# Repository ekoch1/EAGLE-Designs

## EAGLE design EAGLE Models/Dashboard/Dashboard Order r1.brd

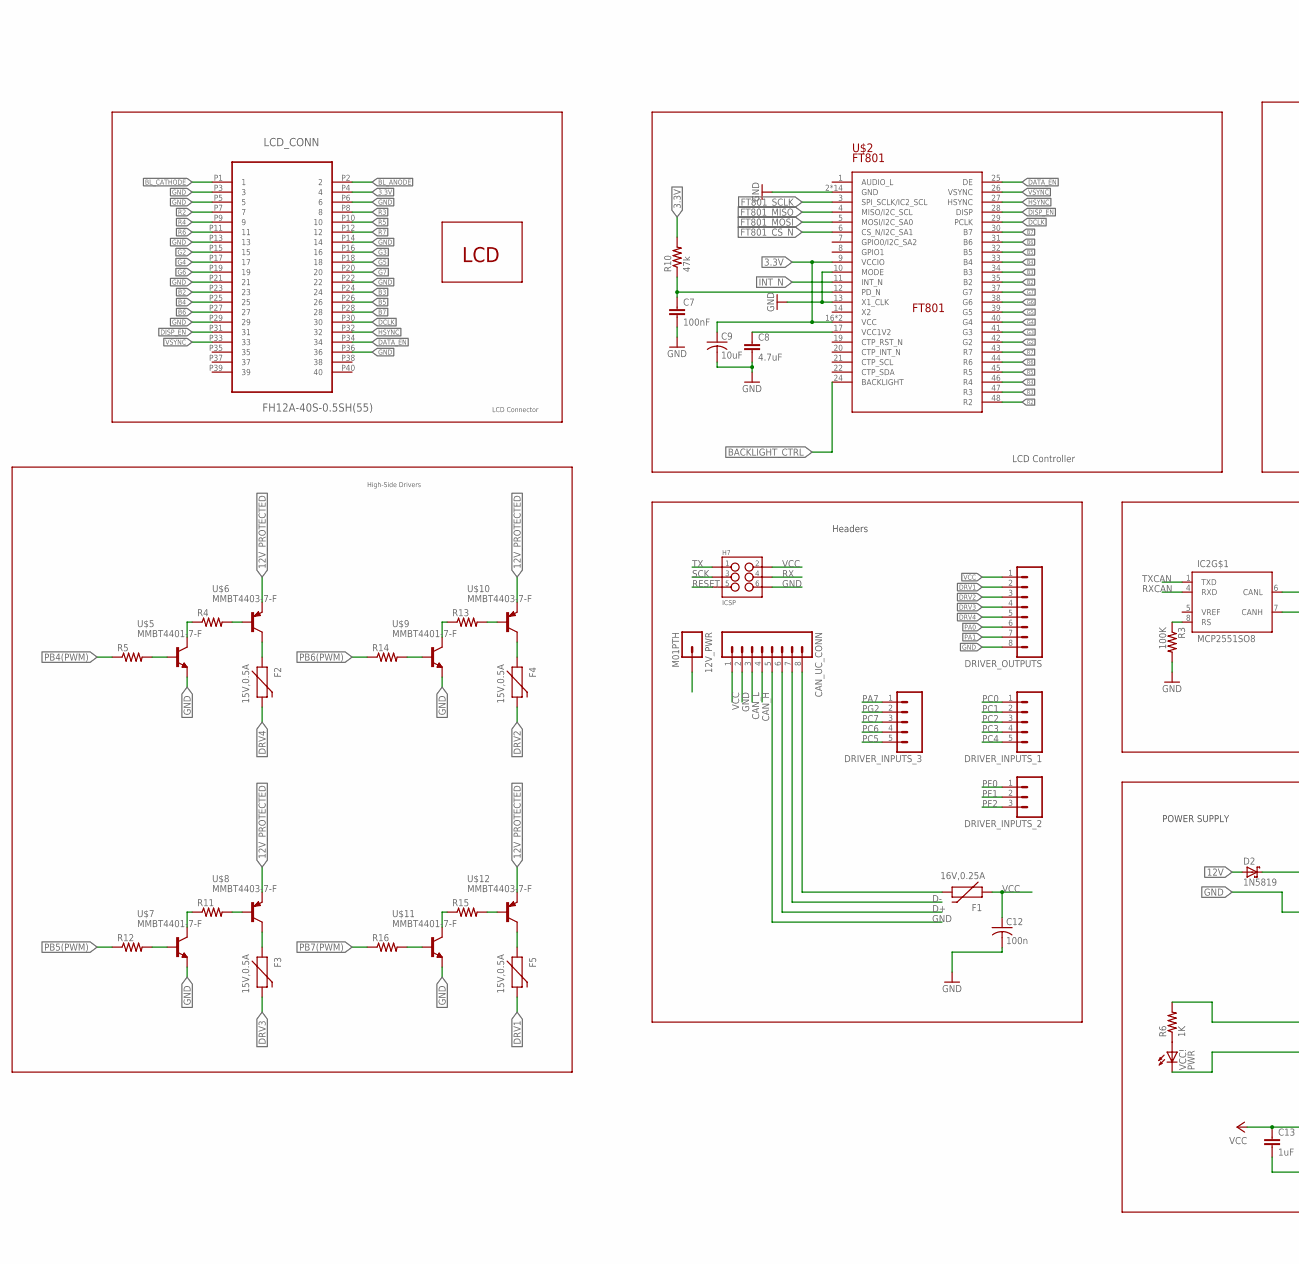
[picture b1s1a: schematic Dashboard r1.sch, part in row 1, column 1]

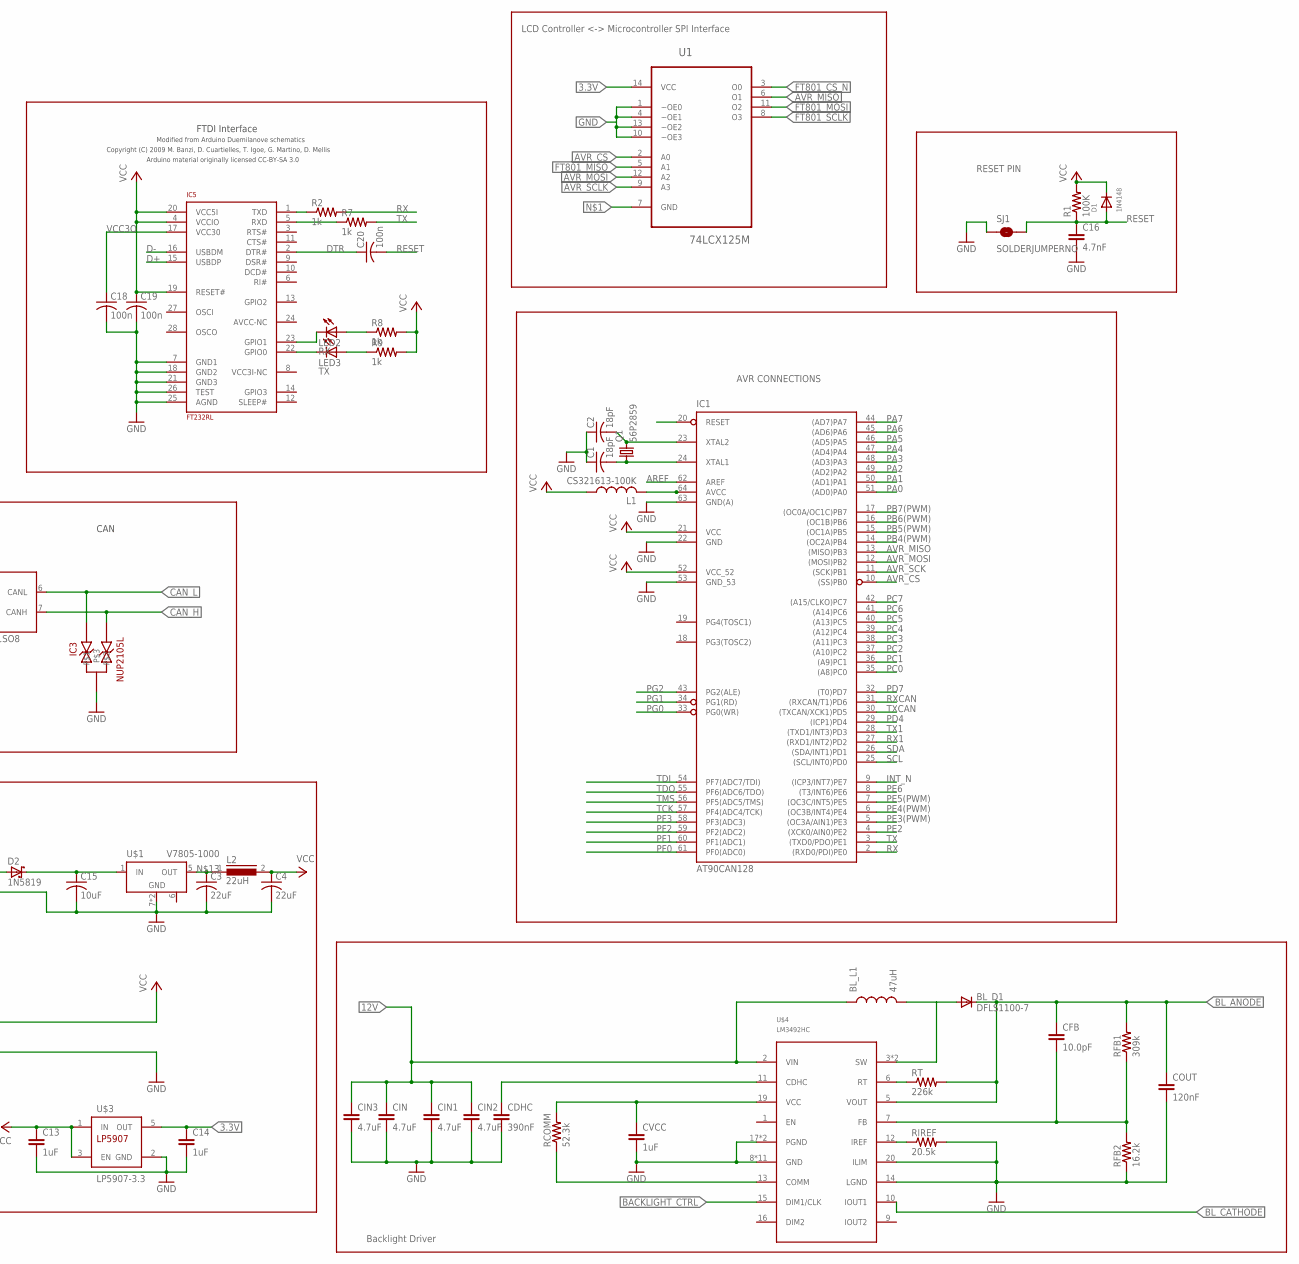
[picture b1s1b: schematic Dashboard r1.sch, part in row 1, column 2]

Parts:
12V_PWR: M01PTH; 1X01
BL_D1: DFLS1100-7; POWERDI-123
BL_L1: 47uH; 2-SMD
C1, C2: 18pF; C0805
C3, C4: 22uF; C2220
C7: 100nF; 0603-CAP
C8: 4.7uF; 0805
C9, C15: 10uF; C2220
C12, C18, C19, C20: 100n; C0805
C13, C14: 1uF; 0603-CAP
C16: 4.7nF; 0805
CAN_UC_CONN: M081X08; 1X08
CDHC: 390nF; 0603-CAP
CFB: 10.0pF; 0603-CAP
CIN, CIN1, CIN2, CIN3: 4.7uF; 0805
COUT: 120nF; 0805
CVCC: 1uF; 0603-CAP
D1: 1N4148; SOD-123
D2: 1N5819; SOD123
DRIVER_INPUTS_1, DRIVER_INPUTS_3: M05PTH; 1X05
DRIVER_INPUTS_2: M03PTH; 1X03
DRIVER_OUTPUTS: M081X08; 1X08
F1: 16V,0.25A; PTC-1206
F2, F3, F4, F5: 15V,0.5A; PTC-1206
H7: ICSP; 2X3_SMD_FCI_54202-G30
IC1: AT90CAN128; TQFP64
IC2: MCP2551SO8; SO08
IC3: NUP2105L; SOT-23
IC5: FT232RL; SSOP28
L1: CS321613-100K; L3216C
L2: 22uH; DR73
LCD_CONN: FH12A-40S-0.5SH(55); HIROSE_FH12A-40S-0.5SH(55)
LED2: RX; CHIPLED_0805
LED3: TX; CHIPLED_0805
Q1: 56P2859; HC49UP
R1, R3: 100K; R0805
R2, R7, R8, R9: 1k; R0805
R4, R5, R11, R12, R13, R14, R15, R16: RESISTOR0603; 0603-RES
R6: 1K; R0805
R10: 47k; 0603-RES
RCOMM: 52.3k; 0603-RES
RFB1: 309k; 0603-RES
RFB2: 16.2k; 0603-RES
RIREF: 20.5k; 0603-RES
RT: 226k; 0603-RES
SJ1: SOLDERJUMPERNO; SJ_2S-NO
U1: 74LCX125M; SOIC127P600X175-14N
U$1: V7805-1000; V78XX-1000
U$2: FT801; RGZ48_5P15X5P15
U$3: LP5907-3.3; SOT23-DBV
U$4: LM3492HC; PWP0020A
U$5, U$7, U$9, U$11: MMBT4401-7-F; SOT-23-3
U$6, U$8, U$10, U$12: MMBT4403-7-F; SOT-23-3
U$13: TCG043WQLBAANN-GN00; TCG043WQLBAANN
VCC!: PWR; CHIPLED_0805

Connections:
3.3V: C9.1, C14.1, LCD_CONN.P4 (4), R10.2, U1.14 (VCC), U$2.9 (VCCIO), U$2.16 (VCC), U$2.18 (VCC), U$3.5 (OUT)
12V: 12V_PWR.1, BL_L1.1, CIN.1, CIN1.1, CIN2.1, CIN3.1, D2.A, U$4.2 (VIN); also elsewhere on the board
12V_PROTECTED: C15.1, D2.C, U$1.1 (IN), U$6.P$3 (E), U$8.P$3 (E), U$10.P$3 (E), U$12.P$3 (E)
AREF: IC1.62 (AREF)
AVR_CS: IC1.10 ((SS)PB0), U1.2 (A0)
AVR_MISO: IC1.13 ((MISO)PB3), U1.6 (O1)
AVR_MOSI: IC1.12 ((MOSI)PB2), U1.12 (A2)
B2: LCD_CONN.P23 (23), U$2.35 (B2)
B3: LCD_CONN.P24 (24), U$2.34 (B3)
B4: LCD_CONN.P25 (25), U$2.33 (B4)
B5: LCD_CONN.P26 (26), U$2.32 (B5)
B6: LCD_CONN.P27 (27), U$2.31 (B6)
B7: LCD_CONN.P28 (28), U$2.30 (B7)
BACKLIGHT_CTRL: U$2.24 (BACKLIGHT), U$4.15 (DIM1/CLK)
BL_ANODE: BL_D1.C, CFB.1, COUT.1, LCD_CONN.P2 (2), RFB1.2, RT.2, U$4.5 (VOUT)
BL_CATHODE: LCD_CONN.P1 (1), U$4.10 (IOUT1)
CAN_H: CAN_UC_CONN.4, IC2.7 (CANH), IC3.2; also elsewhere on the board
CAN_L: CAN_UC_CONN.3, IC2.6 (CANL), IC3.1; also elsewhere on the board
D+: CAN_UC_CONN.6, IC5.15 (USBDP); also elsewhere on the board
D-: CAN_UC_CONN.7, IC5.16 (USBDM); also elsewhere on the board
DATA_EN: LCD_CONN.P34 (34), U$2.25 (DE)
DCLK: LCD_CONN.P30 (30), U$2.29 (PCLK)
DISP_EN: LCD_CONN.P31 (31), U$2.28 (DISP)
DRV1: DRIVER_OUTPUTS.2, F5.2; also elsewhere on the board
DRV2: DRIVER_OUTPUTS.3, F4.2; also elsewhere on the board
DRV3: DRIVER_OUTPUTS.4, F3.2; also elsewhere on the board
DRV4: DRIVER_OUTPUTS.5, F2.2
DTR: C20.1, IC5.2 (DTR#)
FT801_CS_N: U1.3 (O0), U$2.6 (CS_N/I2C_SA1)
FT801_MISO: U1.5 (A1), U$2.4 (MISO/I2C_SCL)
FT801_MOSI: U1.11 (O2), U$2.5 (MOSI/I2C_SA0)
FT801_SCLK: U1.8 (O3), U$2.3 (SPI_SCLK/IC2_SCL)
G2: LCD_CONN.P15 (15), U$2.42 (G2)
G3: LCD_CONN.P16 (16), U$2.41 (G3)
G4: LCD_CONN.P17 (17), U$2.40 (G4)
G5: LCD_CONN.P18 (18), U$2.39 (G5)
G6: LCD_CONN.P19 (19), U$2.38 (G6)
G7: LCD_CONN.P20 (20), U$2.37 (G7)
GND: C1.1, C2.1, C3.2, C4.2, C7.2, C8.2, C9.2, C12.2, C13.2, C14.2, C15.2, C16.2, C18.2, C19.2, CAN_UC_CONN.2, CAN_UC_CONN.5, CDHC.2, CIN.2, CIN1.2, CIN2.2, CIN3.2, COUT.2, CVCC.2, DRIVER_OUTPUTS.8, H7.6, IC1.22 (GND), IC1.53 (GND_53), IC1.63 (GND(A)), IC2.2 (GND), IC3.3, IC5.7 (GND1), IC5.18 (GND2), IC5.21 (GND3), IC5.25 (AGND), IC5.26 (TEST), LCD_CONN.P3 (3), LCD_CONN.P5 (5), LCD_CONN.P6 (6), LCD_CONN.P13 (13), LCD_CONN.P14 (14), LCD_CONN.P21 (21), LCD_CONN.P22 (22), LCD_CONN.P29 (29), LCD_CONN.P36 (36), R3.2, RFB2.1, RIREF.2, SJ1.1, U1.1 (~OE0), U1.4 (~OE1), U1.10 (~OE3), U1.13 (~OE2), U$1.7 (GND), U$1.9 (GND), U$2.2 (GND), U$2.10 (MODE), U$2.13 (X1_CLK), U$2.15 (GND), U$2.23 (GND), U$2.36 (GND), U$2.EP (GND), U$2.V_1 (GND), U$2.V_2 (GND), U$2.V_3 (GND), U$2.V_4 (GND), U$2.V_5 (GND), U$2.V_6 (GND), U$2.V_7 (GND), U$2.V_8 (GND), U$2.V_9 (GND), U$3.2 (GND), U$4.8 (GND), U$4.14 (LGND), U$4.17 (PGND), U$4.18 (PGND), U$4.20 (ILIM), U$4.EP (GND), U$4.P$1 (GND), U$4.P$2 (GND), U$4.P$3 (GND), U$4.P$4 (GND), U$4.P$5 (GND), U$4.P$6 (GND), U$4.P$7 (GND), U$4.P$8 (GND), U$4.P$9 (GND), U$5.P$3 (E), U$7.P$3 (E), U$9.P$3 (E), U$11.P$3 (E), VCC!.C; also elsewhere on the board
HSYNC: LCD_CONN.P32 (32), U$2.27 (HSYNC)
INT_N: IC1.9 ((ICP3/INT7)PE7), U$2.11 (INT_N)
M8RXD: IC5.1 (TXD), R2.1
M8TXD: IC5.5 (RXD), R7.1
unnamed: C8.1, U$2.17 (VCC1V2)
unnamed: C7.1, R10.1, U$2.12 (PD_N)
unnamed: CVCC.1, RCOMM.2, U$4.19 (VCC)
unnamed: RCOMM.1, U$4.13 (COMM)
unnamed: IC2.8 (RS), R3.1
unnamed: CDHC.1, U$4.11 (CDHC)
unnamed: BL_D1.A, BL_L1.2, U$4.3 (SW), U$4.4 (SW)
unnamed: R6.1, VCC!.A
unnamed: CFB.2, RFB1.1, RFB2.2, U$4.7 (FB)
unnamed: C1.2, IC1.24 (XTAL1), Q1.1
unnamed: RT.1, U$4.6 (RT)
unnamed: C3.1, L2.1, U$1.5 (OUT)
unnamed: RIREF.1, U$4.12 (IREF)
unnamed: IC1.64 (AVCC), L1.2
unnamed: R5.2, U$5.P$2 (B)
unnamed: R4.2, U$6.P$2 (B)
unnamed: R4.1, U$5.P$1 (C)
unnamed: F2.1, U$6.P$1 (C)
unnamed: R12.2, U$7.P$2 (B)
unnamed: R11.2, U$8.P$2 (B)
unnamed: R11.1, U$7.P$1 (C)
unnamed: F3.1, U$8.P$1 (C)
unnamed: R14.2, U$9.P$2 (B)
unnamed: IC5.23 (GPIO1), LED2.C
unnamed: R13.2, U$10.P$2 (B)
unnamed: IC5.22 (GPIO0), LED3.C
unnamed: LED2.A, R8.1
unnamed: LED3.A, R9.1
unnamed: R13.1, U$9.P$1 (C)
unnamed: F4.1, U$10.P$1 (C)
unnamed: R16.2, U$11.P$2 (B)
unnamed: R15.2, U$12.P$2 (B)
unnamed: R15.1, U$11.P$1 (C)
unnamed: F5.1, U$12.P$1 (C)
PA0: DRIVER_OUTPUTS.6, IC1.51 ((AD0)PA0)
PA1: DRIVER_OUTPUTS.7, IC1.50 ((AD1)PA1)
PA2: IC1.49 ((AD2)PA2)
PA3: IC1.48 ((AD3)PA3)
PA4: IC1.47 ((AD4)PA4)
PA5: IC1.46 ((AD5)PA5)
PA6: IC1.45 ((AD6)PA6)
PA7: DRIVER_INPUTS_3.1, IC1.44 ((AD7)PA7)
PB4(PWM): IC1.14 ((OC2A)PB4), R5.1
PB5(PWM): IC1.15 ((OC1A)PB5), R12.1
PB6(PWM): IC1.16 ((OC1B)PB6), R14.1
PB7(PWM): IC1.17 ((OC0A/OC1C)PB7), R16.1
PC0: DRIVER_INPUTS_1.1, IC1.35 ((A8)PC0); also elsewhere on the board
PC1: DRIVER_INPUTS_1.2, IC1.36 ((A9)PC1)
PC2: DRIVER_INPUTS_1.3, IC1.37 ((A10)PC2)
PC3: DRIVER_INPUTS_1.4, IC1.38 ((A11)PC3)
PC4: DRIVER_INPUTS_1.5, IC1.39 ((A12)PC4)
PC5: DRIVER_INPUTS_3.5, IC1.40 ((A13)PC5)
PC6: DRIVER_INPUTS_3.4, IC1.41 ((A14)PC6)
PC7: DRIVER_INPUTS_3.3, IC1.42 ((A15/CLKO)PC7)
PD4: IC1.29 ((ICP1)PD4)
PD7: IC1.32 ((T0)PD7)
PE2: IC1.4 ((XCK0/AIN0)PE2)
PE3(PWM): IC1.5 ((OC3A/AIN1)PE3)
PE4(PWM): IC1.6 ((OC3B/INT4)PE4)
PE5(PWM): IC1.7 ((OC3C/INT5)PE5)
PE6: IC1.8 ((T3/INT6)PE6)
PF0: DRIVER_INPUTS_2.1, IC1.61 (PF0(ADC0)); also elsewhere on the board
PF1: DRIVER_INPUTS_2.2, IC1.60 (PF1(ADC1)); also elsewhere on the board
PF2: DRIVER_INPUTS_2.3, IC1.59 (PF2(ADC2)); also elsewhere on the board
PF3: IC1.58 (PF3(ADC3))
PG0: IC1.33 (PG0(WR))
PG1: IC1.34 (PG1(RD))
PG2: DRIVER_INPUTS_3.2, IC1.43 (PG2(ALE))
R2: LCD_CONN.P7 (7), U$2.48 (R2)
R3: LCD_CONN.P8 (8), U$2.47 (R3)
R4: LCD_CONN.P9 (9), U$2.46 (R4)
R5: LCD_CONN.P10 (10), U$2.45 (R5)
R6: LCD_CONN.P11 (11), U$2.44 (R6)
R7: LCD_CONN.P12 (12), U$2.43 (R7)
RESET: C16.1, C20.2, D1.A, H7.5, IC1.20 (RESET), R1.1, SJ1.2
RX: H7.4, IC1.2 ((RXD0/PDI)PE0), R2.2
RX1: IC1.27 ((RXD1/INT2)PD2)
RXCAN: IC1.31 ((RXCAN/T1)PD6), IC2.4 (RXD)
SCK: H7.3
SCL: IC1.25 ((SCL/INT0)PD0)
SDA: IC1.26 ((SDA/INT1)PD1)
TCK: IC1.57 (PF4(ADC4/TCK))
TDI: IC1.54 (PF7(ADC7/TDI))
TDO: IC1.55 (PF6(ADC6/TDO))
TMS: IC1.56 (PF5(ADC5/TMS))
TX: H7.1, IC1.3 ((TXD0/PDO)PE1), R7.2
TX1: IC1.28 ((TXD1/INT3)PD3)
TXCAN: IC1.30 ((TXCAN/XCK1)PD5), IC2.1 (TXD)
USB_V_IN: CAN_UC_CONN.8, F1.2; also elsewhere on the board
VCC: C4.1, C12.1, C13.1, C19.1, CAN_UC_CONN.1, D1.C, DRIVER_OUTPUTS.1, F1.1, H7.2, IC1.21 (VCC), IC1.52 (VCC_52), IC2.3 (VCC), IC5.4 (VCCIO), IC5.19 (RESET#), IC5.20 (VCC5I), L1.1, L2.2, R1.2, R6.2, R8.2, R9.2, U$3.1 (IN), U$3.3 (EN); also elsewhere on the board
VCC3O: C18.1, IC5.17 (VCC30)
VSYNC: LCD_CONN.P33 (33), U$2.26 (VSYNC)
XTAL1: C2.2, IC1.23 (XTAL2), Q1.2

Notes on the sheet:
POWER SUPPLY
CAN
RESET PIN
AVR CONNECTIONS
FTDI Interface
Headers
Modified from Arduino Duemilanove schematics
Copyright (C) 2009 M. Banzi, D. Cuartielles, T. Igoe, G. Martino, D. Mellis
Arduino material originally licensed CC-BY-SA 3.0
LCD Controller
LCD Controller <-> Microcontroller SPI Interface
Backlight Driver
LCD Connector
High-Side Drivers

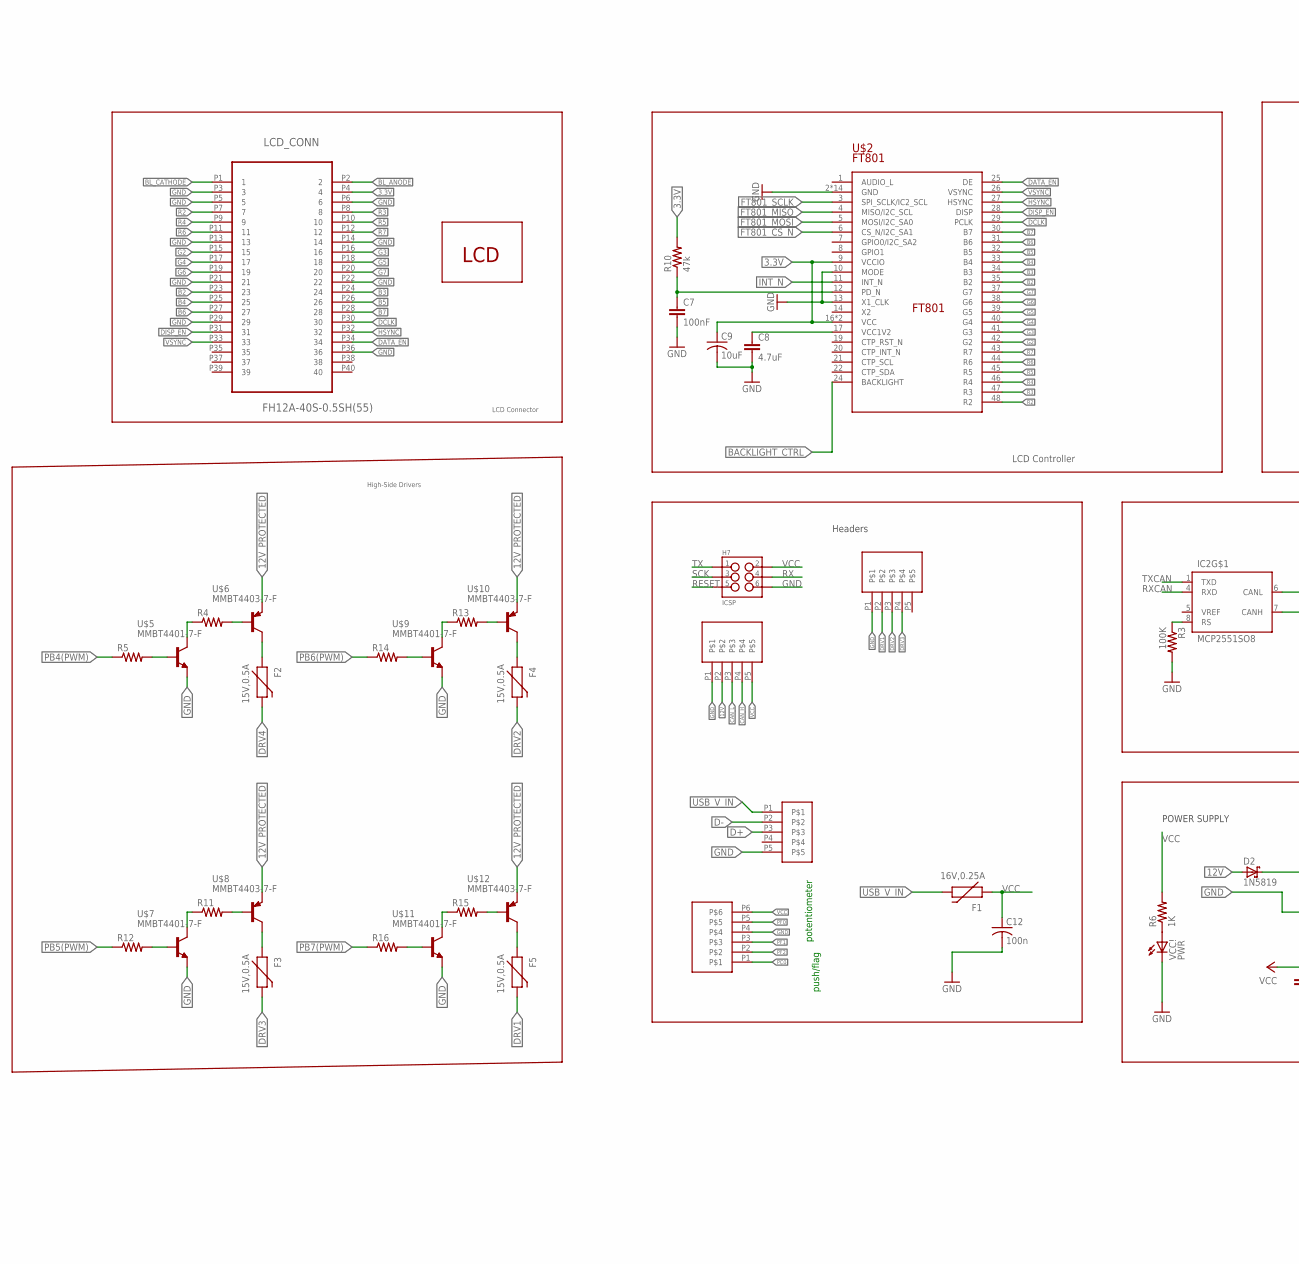
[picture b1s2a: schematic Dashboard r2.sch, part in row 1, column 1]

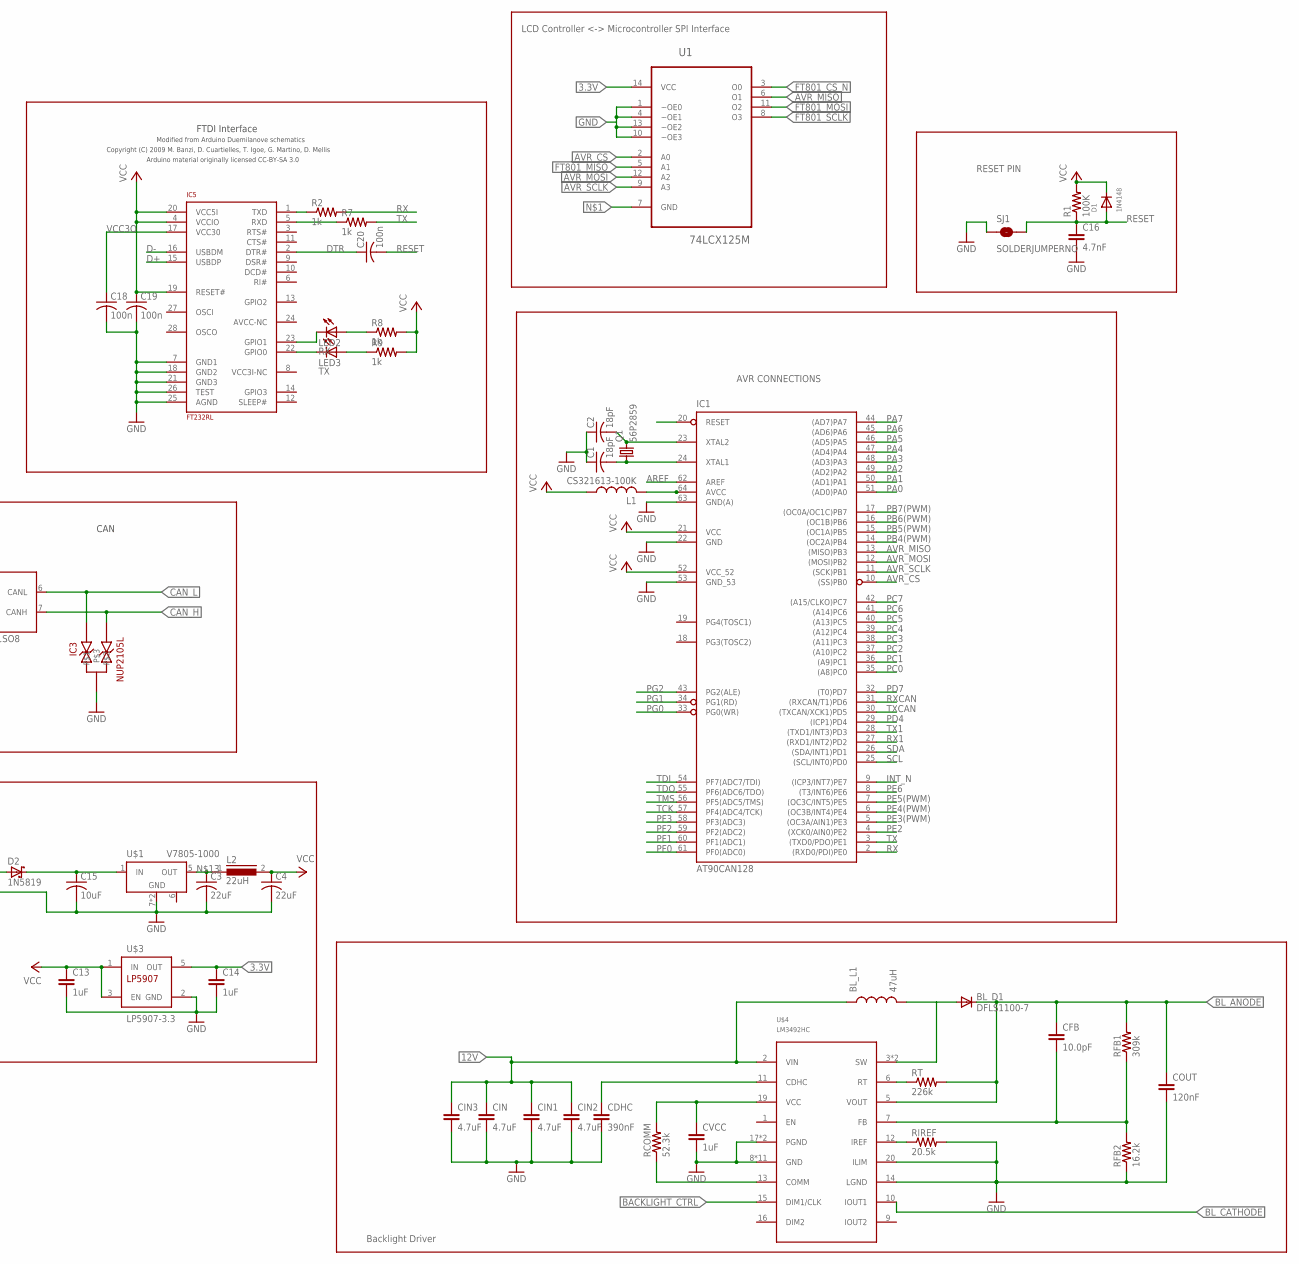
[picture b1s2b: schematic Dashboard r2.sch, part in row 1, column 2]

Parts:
BL_D1: DFLS1100-7; POWERDI-123
BL_L1: 47uH; 2-SMD
C1, C2: 18pF; C0805
C3, C4: 22uF; C2220
C7: 100nF; 0603-CAP
C8: 4.7uF; 0805
C9, C15: 10uF; C2220
C12, C18, C19, C20: 100n; C0805
C13, C14: 1uF; 0603-CAP
C16: 4.7nF; 0805
CANPWR: MICRO5LOCK
CDHC: 390nF; 0603-CAP
CFB: 10.0pF; 0603-CAP
CIN, CIN1, CIN2, CIN3: 4.7uF; 0805
COUT: 120nF; 0805
CVCC: 1uF; 0603-CAP
D1: 1N4148; SOD-123
D2: 1N5819; SOD123
F1: 16V,0.25A; PTC-1206
F2, F3, F4, F5: 15V,0.5A; PTC-1206
H7: ICSP; 2X3_SMD_FCI_54202-G30
IC1: AT90CAN128; TQFP64
IC2: MCP2551SO8; SO08
IC3: NUP2105L; SOT-23
IC5: FT232RL; SSOP28
L1: CS321613-100K; L3216C
L2: 22uH; DR73
LCD_CONN: FH12A-40S-0.5SH(55); HIROSE_FH12A-40S-0.5SH(55)
LED2: RX; CHIPLED_0805
LED3: TX; CHIPLED_0805
LEDOUT: MICRO5LOCK
Q1: 56P2859; HC49UP
R1, R3: 100K; R0805
R2, R7, R8, R9: 1k; R0805
R4, R5, R11, R12, R13, R14, R15, R16: RESISTOR0603; 0603-RES
R6: 1K; R0805
R10: 47k; 0603-RES
RCOMM: 52.3k; 0603-RES
RFB1: 309k; 0603-RES
RFB2: 16.2k; 0603-RES
RIREF: 20.5k; 0603-RES
ROT/PUSH: MICRO6LOCK
RT: 226k; 0603-RES
SJ1: SOLDERJUMPERNO; SJ_2S-NO
U1: 74LCX125M; SOIC127P600X175-14N
U$1: V7805-1000; V78XX-1000
U$2: FT801; RGZ48_5P15X5P15
U$3: LP5907-3.3; SOT23-DBV
U$4: LM3492HC; PWP0020A
U$5, U$7, U$9, U$11: MMBT4401-7-F; SOT-23-3
U$6, U$8, U$10, U$12: MMBT4403-7-F; SOT-23-3
U$13: TCG043WQLBAANN-GN00; TCG043WQLBAANN
U$14: MUSBB
VCC!: PWR; CHIPLED_0805

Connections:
3.3V: C9.1, C14.1, LCD_CONN.P4 (4), R10.2, U1.14 (VCC), U$2.9 (VCCIO), U$2.16 (VCC), U$2.18 (VCC), U$3.5 (OUT)
12V: BL_L1.1, CANPWR.P2, CIN.1, CIN1.1, CIN2.1, CIN3.1, D2.A, U$4.2 (VIN); also elsewhere on the board
12V_PROTECTED: C15.1, D2.C, U$1.1 (IN), U$6.P$3 (E), U$8.P$3 (E), U$10.P$3 (E), U$12.P$3 (E)
AREF: IC1.62 (AREF)
AVR_CS: IC1.10 ((SS)PB0), U1.2 (A0)
AVR_MISO: IC1.13 ((MISO)PB3), U1.6 (O1)
AVR_MOSI: IC1.12 ((MOSI)PB2), U1.12 (A2)
B2: LCD_CONN.P23 (23), U$2.35 (B2)
B3: LCD_CONN.P24 (24), U$2.34 (B3)
B4: LCD_CONN.P25 (25), U$2.33 (B4)
B5: LCD_CONN.P26 (26), U$2.32 (B5)
B6: LCD_CONN.P27 (27), U$2.31 (B6)
B7: LCD_CONN.P28 (28), U$2.30 (B7)
BACKLIGHT_CTRL: U$2.24 (BACKLIGHT), U$4.15 (DIM1/CLK)
BL_ANODE: BL_D1.C, CFB.1, COUT.1, LCD_CONN.P2 (2), RFB1.2, RT.2, U$4.5 (VOUT)
BL_CATHODE: LCD_CONN.P1 (1), U$4.10 (IOUT1)
CAN_H: CANPWR.P4, IC2.7 (CANH), IC3.2; also elsewhere on the board
CAN_L: CANPWR.P3, IC2.6 (CANL), IC3.1; also elsewhere on the board
D+: IC5.15 (USBDP), U$14.P3; also elsewhere on the board
D-: IC5.16 (USBDM), U$14.P2; also elsewhere on the board
DATA_EN: LCD_CONN.P34 (34), U$2.25 (DE)
DCLK: LCD_CONN.P30 (30), U$2.29 (PCLK)
DISP_EN: LCD_CONN.P31 (31), U$2.28 (DISP)
DRV1: F5.2, LEDOUT.P2; also elsewhere on the board
DRV2: F4.2, LEDOUT.P3; also elsewhere on the board
DRV3: F3.2, LEDOUT.P4; also elsewhere on the board
DRV4: F2.2; also elsewhere on the board
DTR: C20.1, IC5.2 (DTR#)
FT801_CS_N: U1.3 (O0), U$2.6 (CS_N/I2C_SA1)
FT801_MISO: U1.5 (A1), U$2.4 (MISO/I2C_SCL)
FT801_MOSI: U1.11 (O2), U$2.5 (MOSI/I2C_SA0)
FT801_SCLK: U1.8 (O3), U$2.3 (SPI_SCLK/IC2_SCL)
G2: LCD_CONN.P15 (15), U$2.42 (G2)
G3: LCD_CONN.P16 (16), U$2.41 (G3)
G4: LCD_CONN.P17 (17), U$2.40 (G4)
G5: LCD_CONN.P18 (18), U$2.39 (G5)
G6: LCD_CONN.P19 (19), U$2.38 (G6)
G7: LCD_CONN.P20 (20), U$2.37 (G7)
GND: C1.1, C2.1, C3.2, C4.2, C7.2, C8.2, C9.2, C12.2, C13.2, C14.2, C15.2, C16.2, C18.2, C19.2, CANPWR.P1, CDHC.2, CIN.2, CIN1.2, CIN2.2, CIN3.2, COUT.2, CVCC.2, H7.6, IC1.22 (GND), IC1.53 (GND_53), IC1.63 (GND(A)), IC2.2 (GND), IC3.3, IC5.7 (GND1), IC5.18 (GND2), IC5.21 (GND3), IC5.25 (AGND), IC5.26 (TEST), LCD_CONN.P3 (3), LCD_CONN.P5 (5), LCD_CONN.P6 (6), LCD_CONN.P13 (13), LCD_CONN.P14 (14), LCD_CONN.P21 (21), LCD_CONN.P22 (22), LCD_CONN.P29 (29), LCD_CONN.P36 (36), LEDOUT.P1, R3.2, RFB2.1, RIREF.2, ROT/PUSH.P4, SJ1.1, U1.1 (~OE0), U1.4 (~OE1), U1.10 (~OE3), U1.13 (~OE2), U$1.7 (GND), U$1.9 (GND), U$2.2 (GND), U$2.10 (MODE), U$2.13 (X1_CLK), U$2.15 (GND), U$2.23 (GND), U$2.36 (GND), U$2.EP (GND), U$2.V_1 (GND), U$2.V_2 (GND), U$2.V_3 (GND), U$2.V_4 (GND), U$2.V_5 (GND), U$2.V_6 (GND), U$2.V_7 (GND), U$2.V_8 (GND), U$2.V_9 (GND), U$3.2 (GND), U$4.8 (GND), U$4.14 (LGND), U$4.17 (PGND), U$4.18 (PGND), U$4.20 (ILIM), U$4.EP (GND), U$4.P$1 (GND), U$4.P$2 (GND), U$4.P$3 (GND), U$4.P$4 (GND), U$4.P$5 (GND), U$4.P$6 (GND), U$4.P$7 (GND), U$4.P$8 (GND), U$4.P$9 (GND), U$5.P$3 (E), U$7.P$3 (E), U$9.P$3 (E), U$11.P$3 (E), U$14.P5, VCC!.C; also elsewhere on the board
HSYNC: LCD_CONN.P32 (32), U$2.27 (HSYNC)
INT_N: IC1.9 ((ICP3/INT7)PE7), U$2.11 (INT_N)
M8RXD: IC5.1 (TXD), R2.1
M8TXD: IC5.5 (RXD), R7.1
unnamed: C8.1, U$2.17 (VCC1V2)
unnamed: C7.1, R10.1, U$2.12 (PD_N)
unnamed: CVCC.1, RCOMM.2, U$4.19 (VCC)
unnamed: RCOMM.1, U$4.13 (COMM)
unnamed: IC2.8 (RS), R3.1
unnamed: CDHC.1, U$4.11 (CDHC)
unnamed: BL_D1.A, BL_L1.2, U$4.3 (SW), U$4.4 (SW)
unnamed: R6.1, VCC!.A
unnamed: CFB.2, RFB1.1, RFB2.2, U$4.7 (FB)
unnamed: C1.2, IC1.24 (XTAL1), Q1.1
unnamed: RT.1, U$4.6 (RT)
unnamed: C3.1, L2.1, U$1.5 (OUT)
unnamed: RIREF.1, U$4.12 (IREF)
unnamed: IC1.64 (AVCC), L1.2
unnamed: R5.2, U$5.P$2 (B)
unnamed: R4.2, U$6.P$2 (B)
unnamed: R4.1, U$5.P$1 (C)
unnamed: F2.1, U$6.P$1 (C)
unnamed: R12.2, U$7.P$2 (B)
unnamed: R11.2, U$8.P$2 (B)
unnamed: R11.1, U$7.P$1 (C)
unnamed: F3.1, U$8.P$1 (C)
unnamed: R14.2, U$9.P$2 (B)
unnamed: IC5.23 (GPIO1), LED2.C
unnamed: R13.2, U$10.P$2 (B)
unnamed: IC5.22 (GPIO0), LED3.C
unnamed: LED2.A, R8.1
unnamed: LED3.A, R9.1
unnamed: R13.1, U$9.P$1 (C)
unnamed: F4.1, U$10.P$1 (C)
unnamed: R16.2, U$11.P$2 (B)
unnamed: R15.2, U$12.P$2 (B)
unnamed: R15.1, U$11.P$1 (C)
unnamed: F5.1, U$12.P$1 (C)
PA0: IC1.51 ((AD0)PA0); also elsewhere on the board
PA1: IC1.50 ((AD1)PA1); also elsewhere on the board
PA2: IC1.49 ((AD2)PA2)
PA3: IC1.48 ((AD3)PA3)
PA4: IC1.47 ((AD4)PA4)
PA5: IC1.46 ((AD5)PA5)
PA6: IC1.45 ((AD6)PA6)
PA7: IC1.44 ((AD7)PA7); also elsewhere on the board
PB4(PWM): IC1.14 ((OC2A)PB4), R5.1
PB5(PWM): IC1.15 ((OC1A)PB5), R12.1
PB6(PWM): IC1.16 ((OC1B)PB6), R14.1
PB7(PWM): IC1.17 ((OC0A/OC1C)PB7), R16.1
PC0: IC1.35 ((A8)PC0), ROT/PUSH.P1; also elsewhere on the board
PC1: IC1.36 ((A9)PC1); also elsewhere on the board
PC2: IC1.37 ((A10)PC2); also elsewhere on the board
PC3: IC1.38 ((A11)PC3); also elsewhere on the board
PC4: IC1.39 ((A12)PC4); also elsewhere on the board
PC5: IC1.40 ((A13)PC5); also elsewhere on the board
PC6: IC1.41 ((A14)PC6); also elsewhere on the board
PC7: IC1.42 ((A15/CLKO)PC7); also elsewhere on the board
PD4: IC1.29 ((ICP1)PD4)
PD7: IC1.32 ((T0)PD7)
PE2: IC1.4 ((XCK0/AIN0)PE2)
PE3(PWM): IC1.5 ((OC3A/AIN1)PE3)
PE4(PWM): IC1.6 ((OC3B/INT4)PE4)
PE5(PWM): IC1.7 ((OC3C/INT5)PE5)
PE6: IC1.8 ((T3/INT6)PE6)
PF0: IC1.61 (PF0(ADC0)), ROT/PUSH.P5; also elsewhere on the board
PF1: IC1.60 (PF1(ADC1)), ROT/PUSH.P3; also elsewhere on the board
PF2: IC1.59 (PF2(ADC2)), ROT/PUSH.P2; also elsewhere on the board
PF3: IC1.58 (PF3(ADC3))
PG0: IC1.33 (PG0(WR))
PG1: IC1.34 (PG1(RD))
PG2: IC1.43 (PG2(ALE)); also elsewhere on the board
R2: LCD_CONN.P7 (7), U$2.48 (R2)
R3: LCD_CONN.P8 (8), U$2.47 (R3)
R4: LCD_CONN.P9 (9), U$2.46 (R4)
R5: LCD_CONN.P10 (10), U$2.45 (R5)
R6: LCD_CONN.P11 (11), U$2.44 (R6)
R7: LCD_CONN.P12 (12), U$2.43 (R7)
RESET: C16.1, C20.2, D1.A, H7.5, IC1.20 (RESET), R1.1, SJ1.2
RX: H7.4, IC1.2 ((RXD0/PDI)PE0), R2.2
RX1: IC1.27 ((RXD1/INT2)PD2)
RXCAN: IC1.31 ((RXCAN/T1)PD6), IC2.4 (RXD)
SCK: H7.3
SCL: IC1.25 ((SCL/INT0)PD0)
SDA: IC1.26 ((SDA/INT1)PD1)
TCK: IC1.57 (PF4(ADC4/TCK))
TDI: IC1.54 (PF7(ADC7/TDI))
TDO: IC1.55 (PF6(ADC6/TDO))
TMS: IC1.56 (PF5(ADC5/TMS))
TX: H7.1, IC1.3 ((TXD0/PDO)PE1), R7.2
TX1: IC1.28 ((TXD1/INT3)PD3)
TXCAN: IC1.30 ((TXCAN/XCK1)PD5), IC2.1 (TXD)
USB_V_IN: F1.2, U$14.P1; also elsewhere on the board
VCC: C4.1, C12.1, C13.1, C19.1, CANPWR.P5, D1.C, F1.1, H7.2, IC1.21 (VCC), IC1.52 (VCC_52), IC2.3 (VCC), IC5.4 (VCCIO), IC5.19 (RESET#), IC5.20 (VCC5I), L1.1, L2.2, R1.2, R6.2, R8.2, R9.2, ROT/PUSH.P6, U$3.1 (IN), U$3.3 (EN); also elsewhere on the board
VCC3O: C18.1, IC5.17 (VCC30)
VSYNC: LCD_CONN.P33 (33), U$2.26 (VSYNC)
XTAL1: C2.2, IC1.23 (XTAL2), Q1.2

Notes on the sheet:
POWER SUPPLY
CAN
RESET PIN
AVR CONNECTIONS
FTDI Interface
Headers
Modified from Arduino Duemilanove schematics
Copyright (C) 2009 M. Banzi, D. Cuartielles, T. Igoe, G. Martino, D. Mellis
Arduino material originally licensed CC-BY-SA 3.0
LCD Controller
LCD Controller <-> Microcontroller SPI Interface
Backlight Driver
LCD Connector
High-Side Drivers
potentiometer
push/flag

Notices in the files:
parts and their libraries:
SparkFun-Capacitors: Licensing: CC v3.0 Share-Alike You are welcome to use this library for commercial purposes.
